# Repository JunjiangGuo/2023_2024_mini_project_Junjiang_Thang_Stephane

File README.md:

# 2023_2024_mini_project_Junjiang_Thang_Stephane

## Introduction
Following the production of the AIME laboratory gas sensor, we aim to develop a system using an ESP32 microcontroller. This system will be designed to gather data from the sensor and transmit the detection of a specific gas to a server via a LoRA module.
Our projects mainly include：
 - The Arduino code for sensors to collect data
 - The PCB shield and KiCad project content
 - The Node-Red to display the dashboard
 - The Datasheet for the sensor

Here is a picture of our circuit: <br>
 <br>

## LoRa
The code in the directory Piste_Verte is a key component of our project, enabling wireless communication over long distances with low power consumption.

<details>
 <summary><b>Pin Configuration</b></summary>
 
```c++
#define rxPin 10
#define txPin 11
```
rxPin and txPin are defined for the serial connection to the LoRa module, allowing for data transmission and reception.
</details>

<details>
 <summary><b>Serial Communication Setup</b></summary>
 
```c++
#define debugSerial Serial
SoftwareSerial mySerial = SoftwareSerial(rxPin, txPin);
#define loraSerial mySerial
```
A virtual serial port (loraSerial) is created for communication with the LoRa module, using the defined rxPin and txPin. The built-in Serial port is used for debugging.
</details>

<details>
 <summary><b>LoRaWAN Configuration</b></summary>
 
```c++
#define freqPlan TTN_FP_EU868
TheThingsNetwork ttn(loraSerial, debugSerial, freqPlan);
```
The frequency plan for LoRaWAN communication is set to TTN_FP_EU868 which is suitable for Europe. The TheThingsNetwork object is initialized with the LoRa and debug serial connections.
</details>

<details>
 <summary><b>TTN Credentials</b></summary>
 
```c++
const char *appEui = "6aadd25252dc20ea";
const char *appKey = "2827F5D8991A743B42BEB51F297AD80A";
```
</details>

<details>
 <summary><b>Data Structure</b></summary>
 
```c++
devicedata_t data = api_DeviceData_init_default;
```
A devicedata_t object is created to structure the sensor data before transmission.
</details>

<details>
 <summary><b>Setup Function</b></summary>
 
```c++
void setup() { ... }
```
In setup(), serial communications are initialized, the LoRa module's status is displayed, and the device attempts to join TTN using the provided credentials.
</details>

<details>
 <summary><b>Main Loop</b></summary>
 
```c++
void loop() { ... }
```
The loop() function reads sensor data, encodes it into bytes, and sends it to TTN every 2 seconds.
</details>

<details>
 <summary><b>Message Reception Function</b></summary>
 
```c++

void message(const uint8_t *payload, size_t length, port_t port) { ... }
```

This function handles incoming messages from TTN, decoding them for ports 100 or higher.
</details>

You can also find the codes:
- [RN2483.ino](https://github.com/JunjiangGuo/2023_2024_mini_project_Junjiang_Thuang_Stephane/blob/master/Piste_Verte/RN2483.ino)

### AIME Sensor
The sensor made at AIME has the following schematics:

There are 10 pins, which are:
- Two N.C. 
- The heating resistor (up to 20V).
- The temperature sensor.
- The gas sensors themselves (2 of them, so we could theorically have two areas for detecting and evene detect different gases).

 ## Circuit amplifier
  The conductance of sensor we use is very low (around ten nS) and is powered by a direct voltage of 12V. The sensor amplifier circuit must then be able to extract information from a very low current signal.
  In this project, we decided to use a transimpedance assembly consisting of an operational amplifier (AOP) to provide a sufficient voltage signal to the analog-to-digital converter (ADC) of an Arduino UNO board.
 
   Our signal is sensitive to amplifier voltage drifts. Our AOP must therefore have a very low input voltage offset so that it cannot distort the signal supplied to the ADC. This restricts our choice of operational amplifier. By shunting this current through a 100 kΩ resistor, the voltage signal supplied to the AOP is 5 mV. For comparison, the [LM741](https://www.ti.com/lit/ds/symlink/lm741.pdf) amplifier has a typical input offset of 1 mV, up to 5 mV. This component is therefore not suitable for our use. So our amplifier must specifically have a low input offset. For this reason, we use the [LTC1050](https://www.analog.com/media/en/technical-documentation/data-sheets/1050fb.pdf), for its drift voltage of 5 µV, or 1000 times weaker than our nominal signal of 5 mV.
 
From this AOP, we develop the architecture of the amplifier circuit. The latter has three filtering stages:
 - at the input, a low-pass filter (R1C1) with a cutoff frequency of 16 Hz filters current noise on the input signal
 - another 1.6 Hz low pass filter (R3C2) coupled to the AOP makes it possible to filter the noise component at 50 Hz coming from the electrical network
 - at the amplifier output, a final filter (R4C4) of 1.6 kHz is used to process noise due to ADC sampling

<div class="row" align="center">
    
    </div>
<p align="center">Figure 1a - Transimpedance amplifier circuit. The *Sensor* resistor represents the strain gauge.</p>

Capacitance C3 is used to filter irregularities in the amplifier supply voltage. Resistor R2 is used to calibrate the amplifier to the desired voltage range, which is that of the ADC of the microcontroller. During the circuit prototyping phase, we used a digital potentiometer in place of this resistor to find its value. Finally, resistor R5 protects the AOP against electrostatic discharges and constitutes an RC filter with capacitance C1 for voltage noise.

<div class="row" align="center">
   
   </div>
<p align="center">Figure 1b - AC simulation of the amplifier circuit. The cutoff frequencies at 1.6 Hz, 16 Hz and 1.6 kHz of the three cascaded filters are visible. This simulation allows us to check the frequency operation of our circuit.</p>

To verify the normal operation of the circuit on LTSpice, we simulate the deformation of the gauge by an input voltage pulse (Figure 2). This voltage pulse generates a variation in the current at the AOP input. Virtually, this represents the change in conductance of the gauge due to its deformation. For this simulation, we vary the conductance from 5 nS to 20 nS, which corresponds to the order of magnitude of the resistive gauges used. In doing so, we scan roughly the entire range of possible input signals:

<div class="row" align="center">
   
   </div>
<p align="center">Figure 2 - Simulation of the operation of the amplifier circuit. A voltage pulse makes it possible to model the deformation of the gauge and the variation of the current signal.</p>

<div class="row" align="center">
   
   </div>
<p align="center">Figure 3 - Simulation results. In blue, the current signal supplied by the gauge and in green the output voltage of the AOP.</p>

## Arduino Integration
The required components are: 
  - 100nF capacitors (3)
  - 1uF capacitor (1) 
  - 100k&Omega; resistors (2)
  - 10k&Omega; resistors (2)
  - 1k&Omega; resistors (2)
  - 100&Omega; resistor (1)
  - LTC1050 pp-amp (1)
  - MCP41100 potentiometer (1) 
  - SLW12 two-position switch (1)
  - Arduino Uno (1)
  - IRF520 NMOS (1)
  - 7-pin header (1) for a LoRa RN2483 module
    <div class="row" align="center">
    
    </div>
  
    <div class="row" align="center">
    
    </div>

    <div class="row" align="center">
    
    </div>
  
    <div class="row" align="center">
     
    </div>
   
    <div class="row" align="center">
     
    </div>
   
    <div class="row" align="center">
     
    </div>
   
 **<p align="center">Figure 4 - PCB design.**</p>
    <div class="row" align="center">
    
    </div>

 **<p align="center">Figure 5 - Components integrated PCB.**</p>

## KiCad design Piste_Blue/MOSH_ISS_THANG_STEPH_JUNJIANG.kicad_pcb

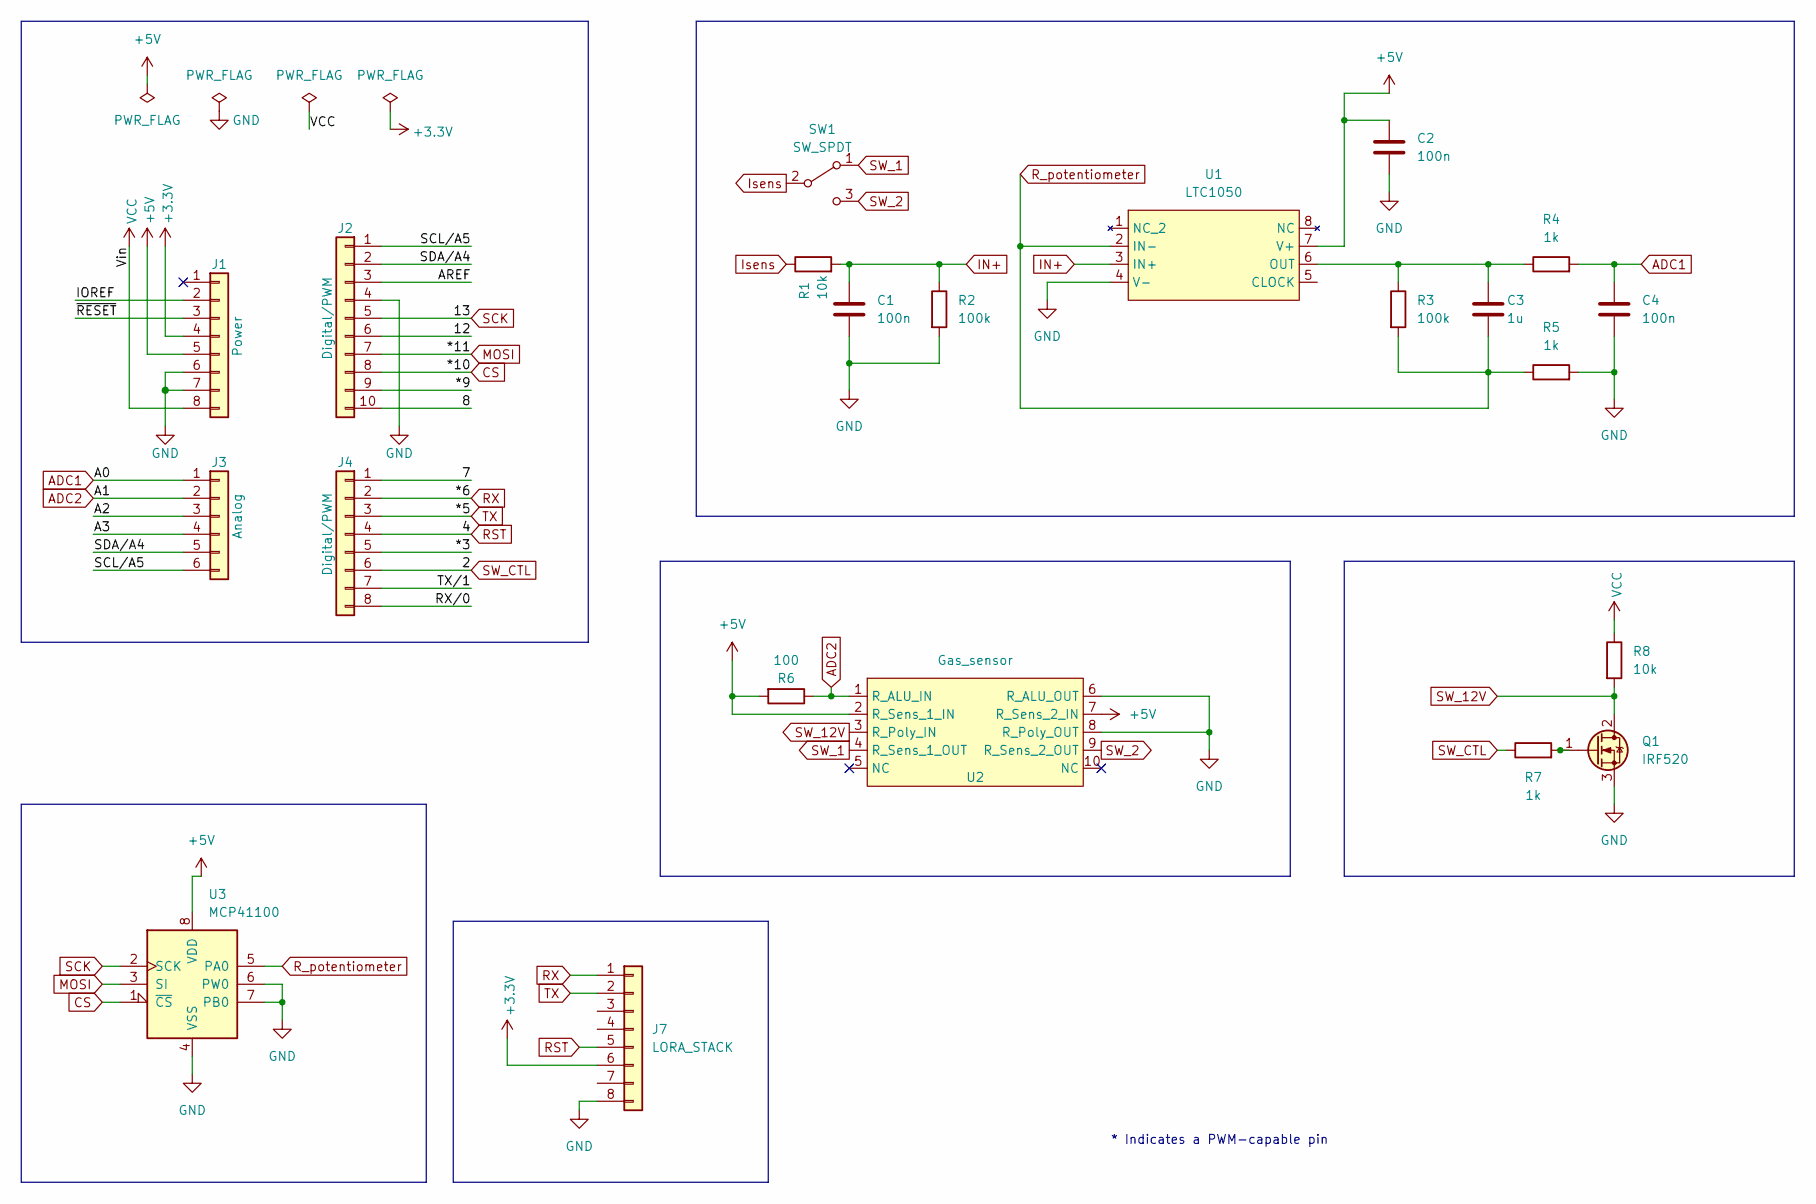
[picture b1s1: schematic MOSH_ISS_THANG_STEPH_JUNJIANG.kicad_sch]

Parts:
C1, C2, C4: 100n; C_Disc_D5.0mm_W2.5mm_P5.00mm
C3: 1u; C_Rect_L9.0mm_W5.1mm_P7.50mm_MKT
J1: Power; PinSocket_1x08_P2.54mm_Vertical
J2: Digital/PWM; PinSocket_1x10_P2.54mm_Vertical
J3: Analog; PinSocket_1x06_P2.54mm_Vertical
J4: Digital/PWM; PinSocket_1x08_P2.54mm_Vertical
J7: LORA_STACK; PinHeader_1x08_P2.54mm_Vertical
Q1: IRF520; TO-220-3_Vertical
R1: 10k; R_Axial_DIN0207_L6.3mm_D2.5mm_P7.62mm_Horizontal
R2, R3: 100k; R_Axial_DIN0207_L6.3mm_D2.5mm_P7.62mm_Horizontal
R4, R5: 1k; R_Axial_DIN0207_L6.3mm_D2.5mm_P7.62mm_Horizontal
R6: 100; R_Axial_DIN0207_L6.3mm_D2.5mm_P10.16mm_Horizontal
R7: 1k; R_Axial_DIN0207_L6.3mm_D2.5mm_P10.16mm_Horizontal
R8: 10k; R_Axial_DIN0207_L6.3mm_D2.5mm_P10.16mm_Horizontal
SW1: SW_SPDT; SW_CuK_OS102011MA1QN1_SPDT_Angled
U1: LTC1050
U2: Gas_sensor; FP_Capteur
U3: MCP41100; DIP-8_W7.62mm

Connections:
+3V3: J1.4, J7.6
+5V: C2.1, J1.5, R6.2, U1.7 (V+), U2.2 (R_Sens_1_IN), U2.7 (R_Sens_2_IN), U3.8 (VDD)
/7: J4.1
/8: J2.10
/12: J2.6
/*3: J4.5
/*9: J2.9
/A2: J3.3
/A3: J3.4
/AREF: J2.3
/IOREF: J1.2
/RX/0: J4.8
/SCL/A5: J2.1, J3.6
/SDA/A4: J2.2, J3.5
/TX/1: J4.7
/~RESET: J1.3
ADC1: C4.1, J3.1, R4.2
ADC2: J3.2, R6.1, U2.1 (R_ALU_IN)
CS: J2.8, U3.1 (~CS)
GND: C1.2, C2.2, C4.2, J1.6, J1.7, J2.4, J7.8, Q1.3 (S), R2.2, R5.2, U1.4 (V-), U2.6 (R_ALU_OUT), U2.8 (R_Poly_OUT), U3.4 (VSS), U3.6 (PW0), U3.7 (PB0)
IN+: C1.1, R1.2, R2.1, U1.3 (IN+)
Isens: R1.1, SW1.2 (B)
MOSI: J2.7, U3.3 (SI)
unnamed: Q1.1 (G), R7.2
unnamed: C3.1, R3.1, R4.1, U1.6 (OUT)
RST: J4.4, J7.5
RX: J4.2, J7.1
R_potentiometer: C3.2, R3.2, R5.1, U1.2 (IN-), U3.5 (PA0)
SCK: J2.5, U3.2 (SCK)
SW_1: SW1.1 (A), U2.4 (R_Sens_1_OUT)
SW_2: SW1.3 (C), U2.9 (R_Sens_2_OUT)
SW_12V: Q1.2 (D), R8.2, U2.3 (R_Poly_IN)
SW_CTL: J4.6, R7.1
TX: J4.3, J7.2
VCC: J1.8, R8.1

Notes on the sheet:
* Indicates a PWM-capable pin

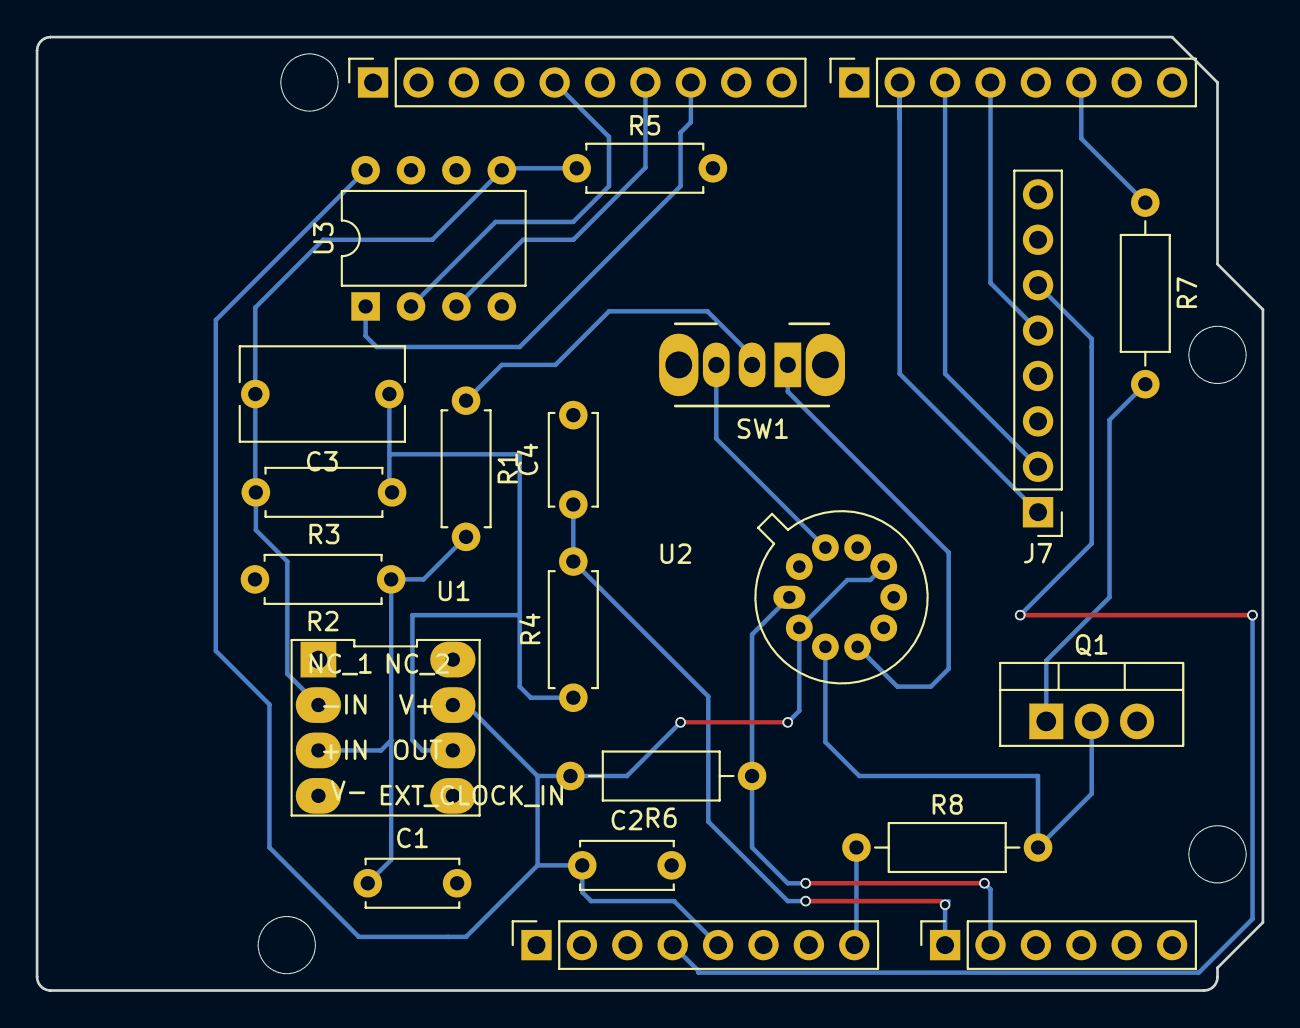
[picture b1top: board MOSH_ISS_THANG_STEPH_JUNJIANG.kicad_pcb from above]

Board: 2 copper layers, 68.6 x 53.3 mm, 26 parts (0 on the bottom side), 23 nets.

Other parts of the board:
MH1, MH2, MH3, MH4: MountingHole_3.2mm

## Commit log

2023-12-15 Piste_Verte fonctionne
2023-12-21 Add files via upload
    add photo
2023-12-21 Add files via upload
    Add Arduino
2024-01-22 Rename image.png to dashboard_lowgas.png
2024-01-27 Create Piste_Noire
